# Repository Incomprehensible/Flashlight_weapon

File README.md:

## Flashlight features
__Two operation modes toggled by selector__

 * Normal light: regular use

 * Emergency mode: blinding light attack

__Variable light intensity, changable with a knob__

__Interchangeable lens__

__Mount for action camera accessories__
<br/><br/>
<br/><br/>
<br/><br/>
<br/><br/>

### Electrical characteristics
* 12.6V - 10.5V input
* ~4.5A input
* 7V output
* 7.5A output
<br/><br/>
<br/><br/>
<br/><br/>
<br/><br/>
## PCB design

Top             |  Bottom
:-------------------------:|:-------------------------:
  |  
 | 

#### Further improvement in design:
* Add a latching circuit with bistable relay to avoid losing power in emergency mode.
* Add suitable input power filtering.

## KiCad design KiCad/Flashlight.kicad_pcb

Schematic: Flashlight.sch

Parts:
C1, C4, C5: C; C_0603_1608Metric_Pad1.08x0.95mm_HandSolder
C2, C7, C8, C9: C; C_0402_1005Metric_Pad0.74x0.62mm_HandSolder
C3: C_Small; C_0402_1005Metric_Pad0.74x0.62mm_HandSolder
C6: CP; C_1210_3225Metric_Pad1.33x2.70mm_HandSolder
C10: C_reserve; C_0402_1005Metric_Pad0.74x0.62mm_HandSolder
D1: D_TVS; SOT-23_Handsoldering
D2: D_Schottky; D_SOD-323_HandSoldering
D3: BLINK_TEST; LED_0603_1608Metric_Pad1.05x0.95mm_HandSolder
D4: PWR_STATUS; LED_0603_1608Metric_Pad1.05x0.95mm_HandSolder
F1: Fuse_PWR; Fuse_1206_3216Metric_Pad1.42x1.75mm_HandSolder
F2: Fuse_LED; Fuse_1206_3216Metric_Pad1.42x1.75mm_HandSolder
J2: XHP90
J3: XT30PW-F; AMASS_XT30PW-F; Manufacturer_Part_Number XT30PW-F
J4: ICSP 1x6; B6B-EH-A
Q1: PMOS_Vin; YJS4407A
R1: R; R_0603_1608Metric_Pad0.98x0.95mm_HandSolder
R2, R3: 10k; R_0402_1005Metric_Pad0.72x0.64mm_HandSolder
R4, R5, R6, R7, R8, R10, R23: R; R_0402_1005Metric_Pad0.72x0.64mm_HandSolder
S1: SS-12D06L5; SS12D06L5; Manufacturer_Part_Number SS-12D06L5
SW1: SW_SPST; DSIC01LSGET
SW2: SW_Push; SW_TS-1187A-B-A-B
TP1: 5V; TestPoint_Pad_D2.0mm
TP2: VDD; TestPoint_Pad_D2.0mm
TP3: GND; TestPoint_Pad_D2.0mm
TP4: LED+; TestPoint_Pad_D2.0mm
U1: AMS1117-5.0; SOT-223-3_TabPin2
U2: PIC16F716-ISO; SOIC127P1030X265-18N
U3: LM60BIM3
Y1: Crystal; Crystal_SMD_3225-4Pin_3.2x2.5mm_HandSoldering

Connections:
+5V: C4.2, C6.1, C10.1, J4.2, R3.1, R4.1, R8.2, R10.1, TP1.1, U1.2 (VO), U2.14 (VDD), U3.1 (VS+); also elsewhere on the board
ANALOG_TEMP: U2.17 (AN0/RA0), U3.2 (VO)
CLK: J4.5, U2.12 (P1C/RB6)
DATA: J4.4, U2.13 (P1D/RB7)
ENABLE_DCDC: C2.1, R10.2, SW1.2 (B), U2.10 (~ECCPAS0~/RB4)
LED_GND: C1.2, C2.2, C3.2, C4.1, C5.2, C6.2, C7.2, C8.1, C9.1, C10.2, D1.2 (A2), D3.1 (K), D4.1 (K), J2.1, J3.1, J4.3, R1.1, R2.2, R5.2, R6.2, R23.2, TP3.1, U1.1 (GND), U2.5 (VSS), U3.3 (GND); also elsewhere on the board
LED_VDD: F2.2, TP4.1; also elsewhere on the board
MODE: C7.1, R4.2, S1.2 (COM), U2.6 (INT/~ECCPAS2~/RB0)
unnamed: C3.1, J3.3, J3.4, R2.1
unnamed: C8.2, U2.16 (OSC1/CLKI), Y1.2
unnamed: C9.2, U2.15 (OSC2/CLKO), Y1.1
unnamed: D2.2 (A), R3.2
unnamed: D3.2 (A), R7.2
unnamed: D4.2 (A), R8.1
unnamed: F1.2, Q1.1, Q1.2, Q1.3
unnamed: F2.1, J2.2
unnamed: Q1.4, R1.2
unnamed: R5.1, SW2.1
unnamed: R6.1, S1.1 (NO)
unnamed: R7.1, U2.8 (T1OSI/RB2)
unnamed: R23.1, SW1.1 (A)
RELAY: U2.11 (P1B/RB5); also elsewhere on the board
SHUTDOWN: U2.1 (AN2/RA2); also elsewhere on the board
VIN: C1.1, C5.1, D1.1 (A1), F1.1, TP2.1, U1.3 (VI); also elsewhere on the board
VPP\RST: D2.1 (K), J4.1, SW2.2, U2.4 (~MCLR~/Vpp)
VXT: J3.2, Q1.5, Q1.6, Q1.7, Q1.8

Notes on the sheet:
Filtering
TODO: 1. remove terminal or not 12. review schematics with Kolya 13. make BOM 14. create footprints 15. draw an example of board
Reverse plug protection
1k5
20 MHz
10uF
22uF
Power input
Protection & filtering
LED input
Testpoints & indication
DC-DC 5V
ICSP header
PIC controller
13 V
Signals & inputs
56nF
27pF
500
Overcurrent+ESD protection
10k
Analog input

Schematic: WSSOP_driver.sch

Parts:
C11: Cff; C_0805_2012Metric_Pad1.18x1.45mm_HandSolder
C12: Cout; CAP_10TPE47MAZB; PARTREV 30-Nov-20
C13: C_reserve; C_0402_1005Metric_Pad0.74x0.62mm_HandSolder
C15: Cvcc; C_0805_2012Metric_Pad1.18x1.45mm_HandSolder
C16, C17: Cin; C_0805_2012Metric_Pad1.18x1.45mm_HandSolder
C18: Cadj; C_0402_1005Metric_Pad0.74x0.62mm_HandSolder
D5: Driver_Schottky; TO-263-2
D6: D_flyback; D_SMAG
H1, H2, H3, H4: MountingHole; MountingHole_2.5mm_Pad_Via
H5, H6: BMS_mnt; MountingHole_2.2mm_M2_Pad
K1: HFD4-24-SR; HFD4024S
L1: L; IHLP4040DZER2R2M01
Q2: CSD25402Q3A; TRANS_CSD25402Q3A; PARTREV B
Q3, Q4: Q_NMOS_GSD; SOT-23_Handsoldering
R9: Rsns; R_1508_Wide
R11: Rfb2; R_0402_1005Metric_Pad0.72x0.64mm_HandSolder
R12: Rfb1; R_0805_2012Metric_Pad1.20x1.40mm_HandSolder
R13: Rt; R_0402_1005Metric_Pad0.72x0.64mm_HandSolder
R14: R; R_0603_1608Metric_Pad0.98x0.95mm_HandSolder
R15: R_cushion; TyoHM-SMF-3W
R16, R19, R22: R; R_0402_1005Metric_Pad0.72x0.64mm_HandSolder
R17: Rterm; R_0402_1005Metric_Pad0.72x0.64mm_HandSolder
R18: Rpar; R_0603_1608Metric_Pad0.98x0.95mm_HandSolder
R20: Radj; R_0603_1608Metric_Pad0.98x0.95mm_HandSolder
R21: R_Variable; VZ067TL1B
TH2: Thermistor_NTC; R_0603_1608Metric_Pad0.98x0.95mm_HandSolder
U4: LM25085MM_NOPB; LM25085MM&slash_NOPB

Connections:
+5V: R15.2; also elsewhere on the board
ADJ: C18.2, R20.1, R21.2, U4.1
FB: C11.2, R11.1, R12.2, U4.3
ISEN: Q2.9, Q2.9_1, Q2.9_2, Q2.9_3, Q2.9_4, Q2.9_5, Q2.9_6, Q2.9_7, R9.1, TH2.1, U4.5
LED_GND: C12.2, C13.2, C16.2, C17.2, D5.1 (A), D5.3 (A), Q3.2 (S), Q4.2 (S), R12.1, R17.1, R22.1, TH2.2, U4.4; also elsewhere on the board
LED_VDD: C11.1, C12.1, C13.1, L1.2, R11.2; also elsewhere on the board
unnamed: C15.1, U4.7
unnamed: D5.4 (K), L1.1, Q2.1, Q2.2, Q2.3
unnamed: D6.1 (K), K1.1, R15.1
unnamed: D6.2 (A), K1.8, Q4.3 (D)
unnamed: K1.2, R18.2
unnamed: Q2.4, U4.6
unnamed: Q3.1 (G), R16.1, R17.2
unnamed: Q3.3 (D), R14.1
unnamed: Q4.1 (G), R19.2, R22.2
unnamed: R18.1, R21.1
RELAY: R19.1; also elsewhere on the board
RT: R13.1, R14.2, U4.2
SHUTDOWN: R16.2; also elsewhere on the board
VIN: C15.2, C16.1, C17.1, C18.1, K1.3, R9.2, R13.2, R20.2, U4.8; also elsewhere on the board

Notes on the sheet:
10uF
470nF 1mOhm Low ESR close to the pins
10mOhm
-20V -75Amps
1.05V 20A
2.2uH 10mOhm
2nF 1mOhm
10k
2.18k
33uF 70mOhm Tantalum
60.4k
https://tinyurl.com/yg4wk7xr Simulation: https://webench.ti.com/power-designer/switching-regulator/customize/15
500
https://tinyurl.com/ygr74bbu
Shutdown circuit
LED driver
Mounting holes
Current limit regulator
Radj: 3.16k for 12.64 A 2k for 8A Formula: (40 / 1000000) * (Radj / Rsense)
1nF 0Ohm
3.16k 0603
Normal light mode: Radj = 3.16k Rparallel = 1.5k + Rpot(=0) Ilim = (40 / 1000000) * (1017.17 / 0.01) = 4A
Power characteristics: DC Vin: 10.5V - 12.6V Iin: 5A (IC input: 4.59A) Vout: 7V Iout: 7.5 A Pout: 52.5W Freq: 610.31 kHz SW Ipk: 8.59A Total Pd: 5.33W
Current limit calculation Min current limit threshold value (Icl) is max Iload + max Iripple/2. Resulting Iload = Icl - Iripple/2 Icl: 8.59A (peak switch current/min limit current value) Iload: 7.5A (max load current) Iinductor: 2.19A (p-p inductor ripple current) Formula: Icl = Iload+Iinductor/2 =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

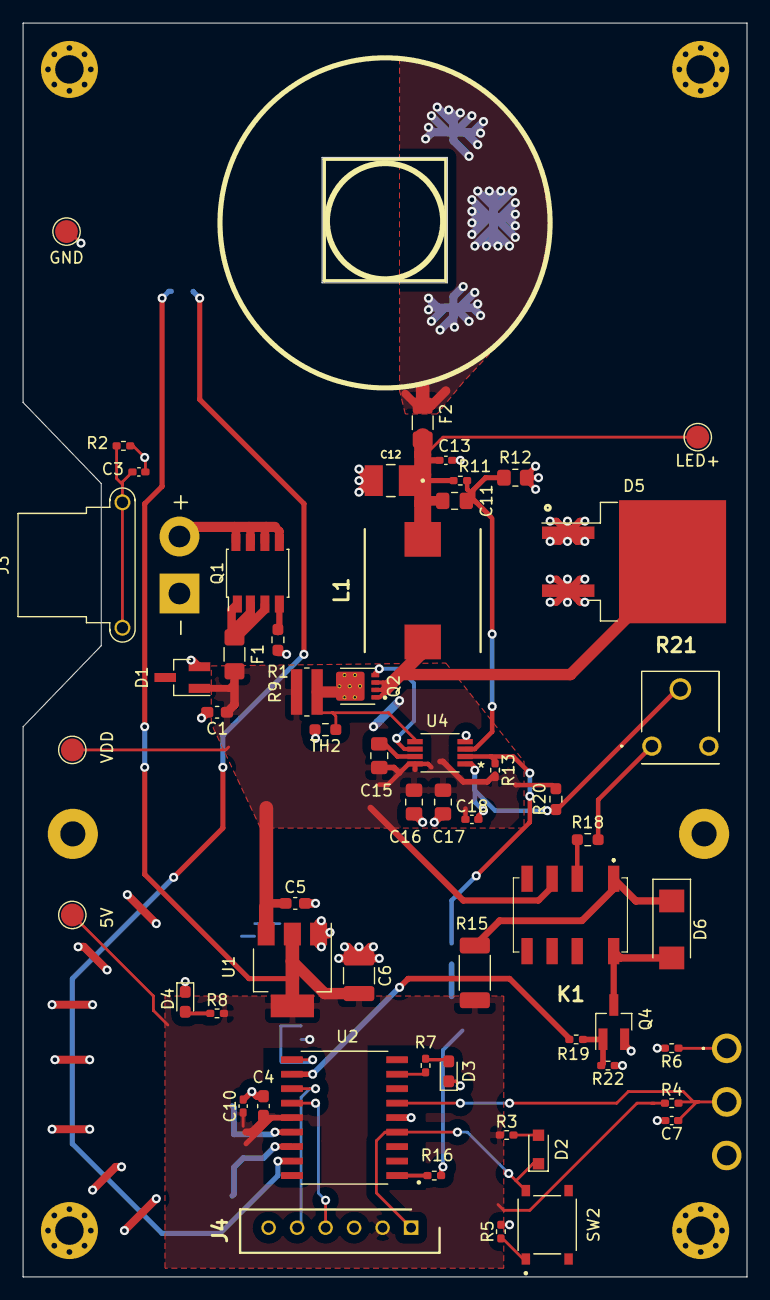
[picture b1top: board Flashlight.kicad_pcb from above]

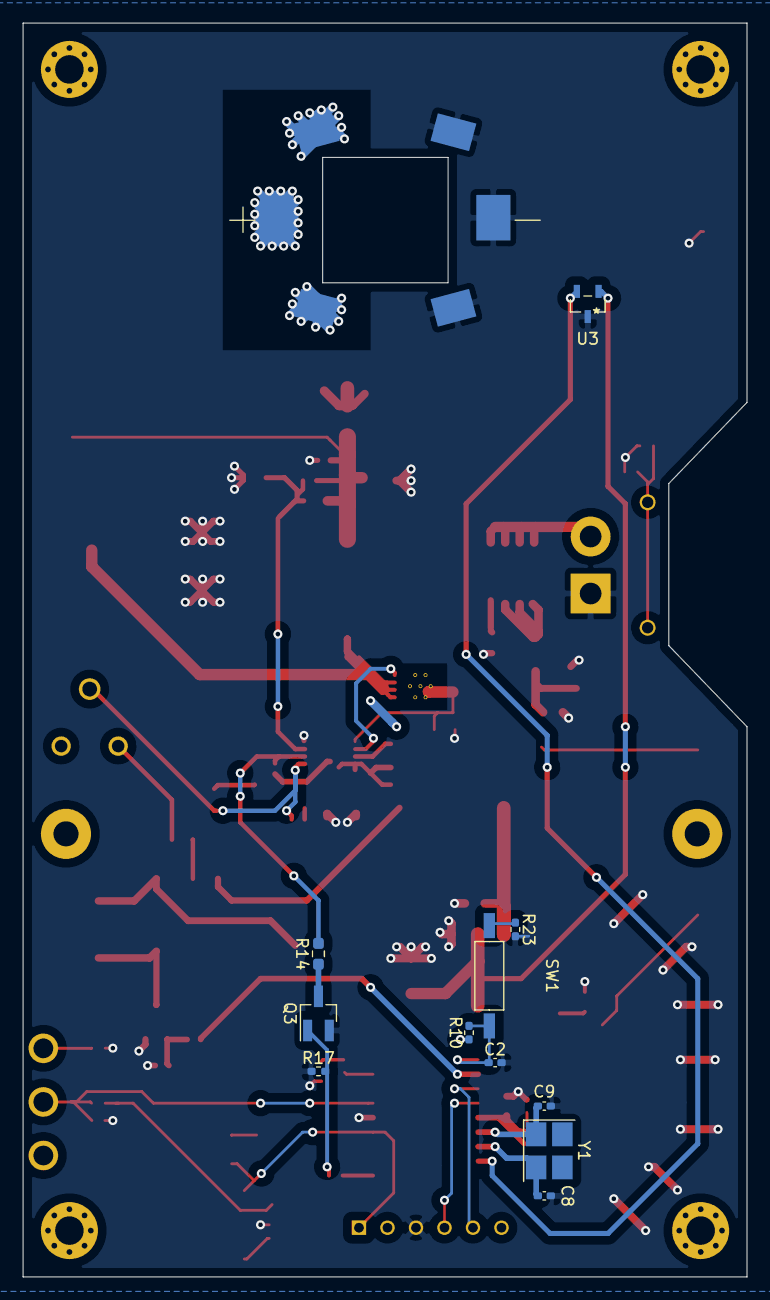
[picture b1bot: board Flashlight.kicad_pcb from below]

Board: 2 copper layers, 63.5 x 110.0 mm, 76 parts (12 on the bottom side), 40 nets.

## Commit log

2021-11-05 Initial schematics.
2021-11-05 Removed screw terminal, power input selection and ferrite bead filter.
2021-12-03 Latest schematics, all footprints except LED.
2022-01-15 Finished routing the first version of a PCB. WSON is out of stock so new driver was used.
2022-07-25 Update README.
2022-09-14 Added basic software.
2022-10-14 Add 3d models
    Added Fusion 360 archive project, step production files for order in factory, 3mf files for self-made on 3d printers.
2022-10-15 Working on README...
2022-10-15 Add some renders and graphic files
2022-10-16 Add renders
2022-10-16 Ready to merge request i think
2022-10-16 Edit graphics for Nad requirements
2022-10-16 Reupload 3d models for new decal graphics
2022-10-16 Change renders for right ones
